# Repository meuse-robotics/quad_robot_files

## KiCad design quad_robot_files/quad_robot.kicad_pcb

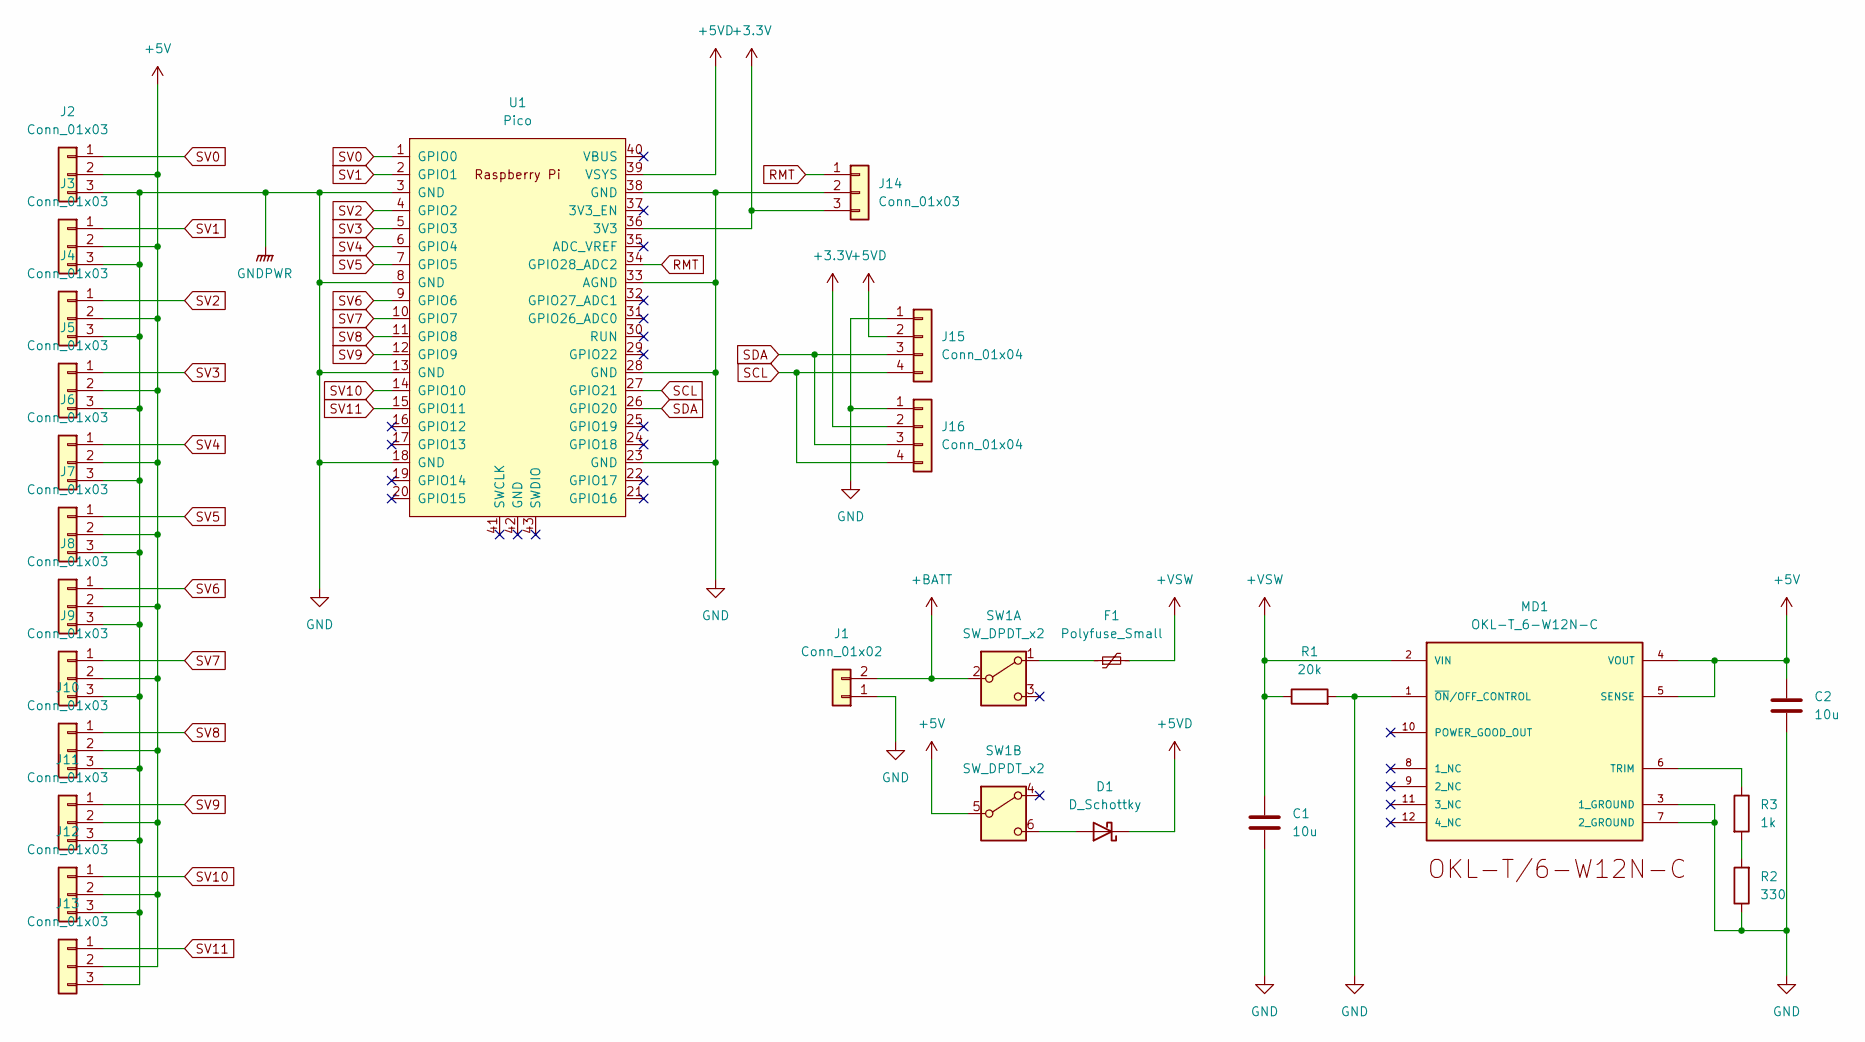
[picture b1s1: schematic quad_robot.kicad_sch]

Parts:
C1, C2: 10u; CP_Radial_D5.0mm_P2.50mm
D1: D_Schottky; D_A-405_P7.62mm_Horizontal
F1: Polyfuse_Small; Fuse_BelFuse_0ZRE0055FF_L14.0mm_W4.1mm
J1: Conn_01x02; PinHeader_1x02_P2.54mm_Vertical
J2, J3, J4, J5, J6, J7, J8, J9, J10, J11, J12, J13, J14: Conn_01x03; PinHeader_1x03_P2.54mm_Vertical
J15, J16: Conn_01x04; PinHeader_1x04_P2.00mm_Vertical
MD1: OKL-T_6-W12N-C; MURATA_OKL-T-6-W12N-C_0; MOUSER_PART_NUMBER 580-OKL-T/6-W12N-C; MOUSER_DESCRIPTION Non-Isolated DC/DC Converters 12Vin .59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
R1: 20k; R_Axial_DIN0204_L3.6mm_D1.6mm_P7.62mm_Horizontal
R2: 330; R_Axial_DIN0204_L3.6mm_D1.6mm_P7.62mm_Horizontal
R3: 1k; R_Axial_DIN0204_L3.6mm_D1.6mm_P7.62mm_Horizontal
SW1: SW_DPDT_x2; SW_CK_JS202011CQN_DPDT_Straight
U1: Pico; RPi_Pico_SMD_TH

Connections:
+3.3V: J14.3, J16.2, U1.36 (3V3)
+5V: C2.1, J2.2, J3.2, J4.2, J5.2, J6.2, J7.2, J8.2, J9.2, J10.2, J11.2, J12.2, J13.2, MD1.4 (VOUT), MD1.5 (SENSE), SW1.5 (B)
+5VD: D1.1 (K), J15.2, U1.39 (VSYS)
+BATT: J1.2, SW1.2 (B)
+VSW: C1.1, F1.2, MD1.2 (VIN), R1.1
GND: C1.2, C2.2, J1.1, J2.3, J3.3, J4.3, J5.3, J6.3, J7.3, J8.3, J9.3, J10.3, J11.3, J12.3, J13.3, J14.2, J15.1, J16.1, MD1.1 (~ON/OFF_CONTROL), MD1.3 (1_GROUND), MD1.7 (2_GROUND), R1.2, R2.1, U1.3 (GND), U1.8 (GND), U1.13 (GND), U1.18 (GND), U1.23 (GND), U1.28 (GND), U1.33 (AGND), U1.38 (GND)
unnamed: D1.2 (A), SW1.6 (C)
unnamed: MD1.6 (TRIM), R3.1
unnamed: R2.2, R3.2
unnamed: F1.1, SW1.1 (A)
RMT: J14.1, U1.34 (GPIO28_ADC2)
SCL: J15.4, J16.4, U1.27 (GPIO21)
SDA: J15.3, J16.3, U1.26 (GPIO20)
SV0: J2.1, U1.1 (GPIO0)
SV1: J3.1, U1.2 (GPIO1)
SV2: J4.1, U1.4 (GPIO2)
SV3: J5.1, U1.5 (GPIO3)
SV4: J6.1, U1.6 (GPIO4)
SV5: J7.1, U1.7 (GPIO5)
SV6: J8.1, U1.9 (GPIO6)
SV7: J9.1, U1.10 (GPIO7)
SV8: J10.1, U1.11 (GPIO8)
SV9: J11.1, U1.12 (GPIO9)
SV10: J12.1, U1.14 (GPIO10)
SV11: J13.1, U1.15 (GPIO11)

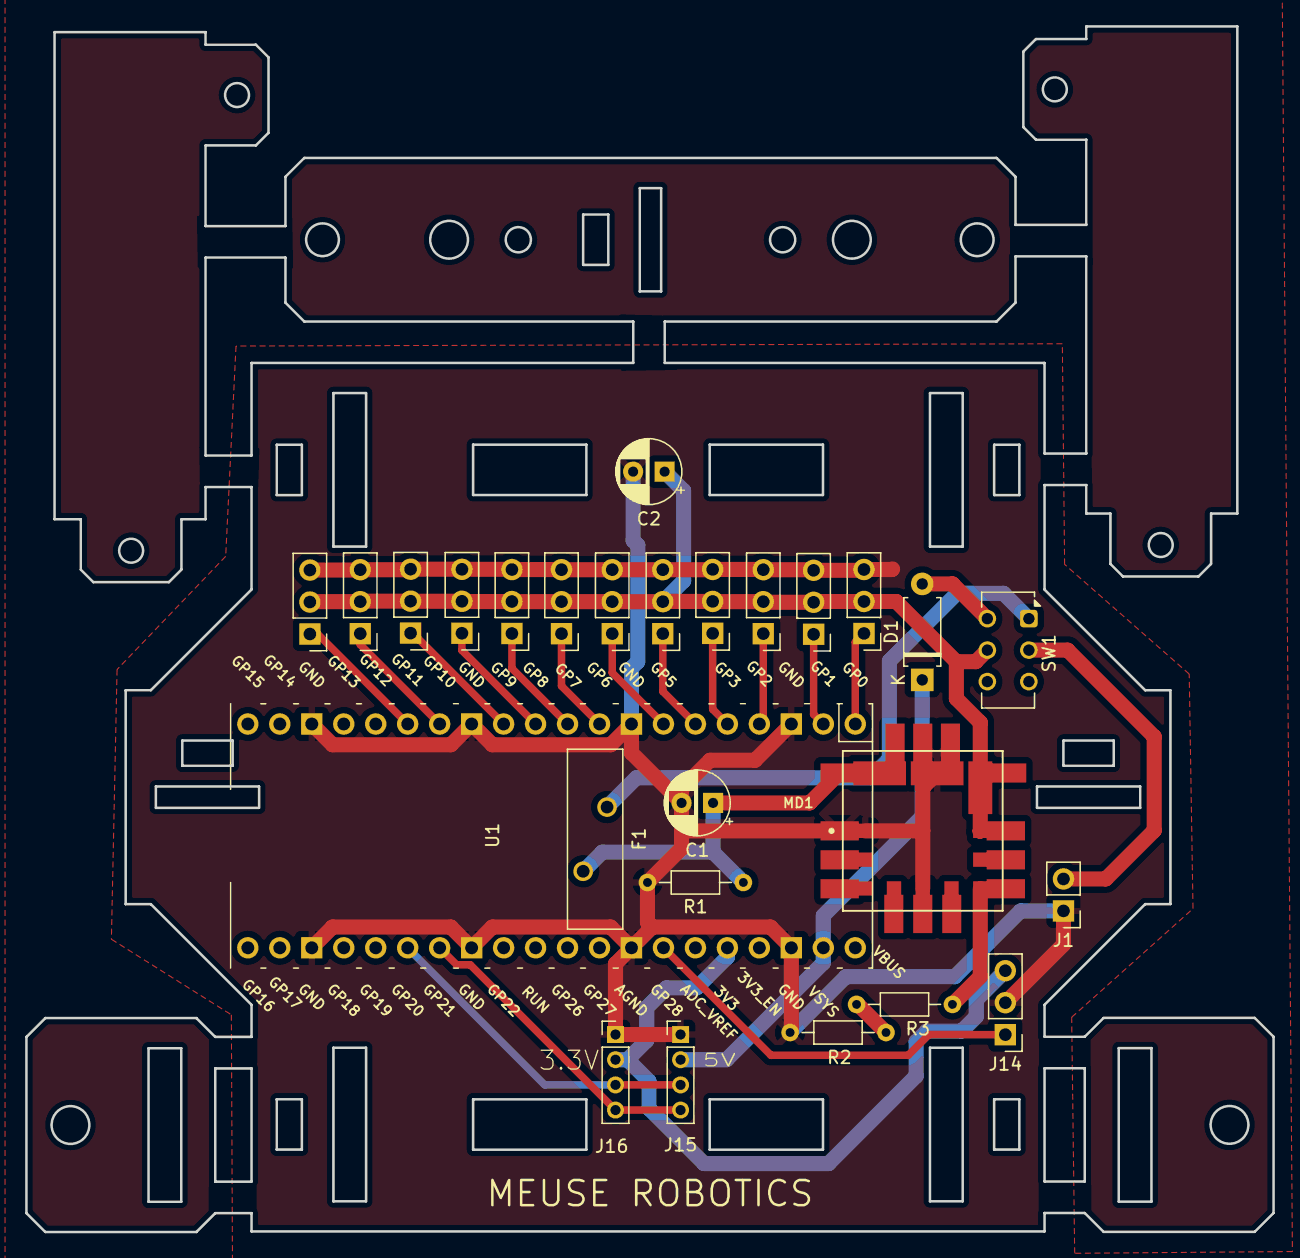
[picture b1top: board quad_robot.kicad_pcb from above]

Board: 2 copper layers, 99.1 x 95.8 mm, 26 parts (0 on the bottom side), 25 nets.

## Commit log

2024-07-02 uploaded
2024-07-05 add chap7 files
2024-07-05 Create file
2024-07-05 add files
